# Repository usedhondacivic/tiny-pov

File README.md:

# tiny-pov

Work in progress, check back soon for more.

[Checkout the GUI](http://michael-crum.com/tiny-pov/) for a sneak peak.

Tiny-pov is a low cost, high performance, persistence of vision display built with the STM32G0.
This project is designed to explore cost effective and easily manufacturable mechatronic design.

I currently plan to use a STM32G0 to relay data from a SD Card directly into a string of APA102 LEDs. The arm will be inductively powered using custom coils.

See my first revision of the POV display here: https://github.com/usedhondacivic/ECE-4760-POV-Display

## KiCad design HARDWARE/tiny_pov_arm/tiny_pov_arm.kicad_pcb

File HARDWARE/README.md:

# Hardware

The Tiny-pov circuit boards were designed using [SKiDL](https://devbisme.github.io/skidl/), a python library for generating KiCAD schematics from python code. 
The SKiDL source code for the PCBs is found in `arm_board.py` and `motor_board.py`. The KiCAD symbol and schematic libraries for all components is included, so it should run without any hassle.

```cd HARDWARE && python3 arm_board.py```

For power delivery, I designed a custom 3D printed inductive power coupling inspired by electric toothbrushes. It uses a core of [ferrous 3D printer filament](https://proto-pasta.com/products/magnetic-iron-pla) to increase the efficiency of transformer.
You can find the design files on [OnShape](https://cad.onshape.com/documents/c43b3a736df7726a49e53755/w/ad83221bbc41dda85aa40265/e/0c03297652a8e1a4c52ec09d?renderMode=0&uiState=655283aa916fc55b212fd806).

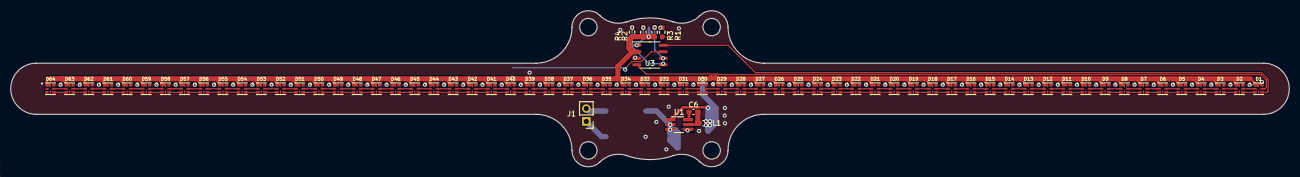
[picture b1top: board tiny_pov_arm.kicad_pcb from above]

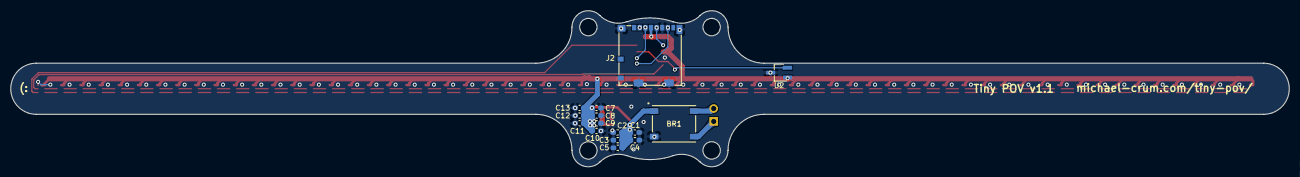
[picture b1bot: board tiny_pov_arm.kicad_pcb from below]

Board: 2 copper layers, 250.0 x 30.5 mm, 88 parts (15 on the bottom side), 140 nets.

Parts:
BR1: DBF310-13; DBF_DIO
C1, C2, C3, C4, C5, C7, C8, C9, C10, C11, C12, C13: 22 uF; C_0603_hand_solder
C6: 100 nF; C_0603_hand_solder
D1, D2, D3, D4, D5, D6, D7, D8, D9, D10, D11, D12, D13, D14, D15, D16, D17, D18, D19, D20, D21, D22, D23, D24, D25, D26, D27, D28, D29, D30, D31, D32, D33, D34, D35, D36, D37, D38, D39, D40, D41, D42, D43, D44, D45, D46, D47, D48, D49, D50, D51, D52, D53, D54, D55, D56, D57, D58, D59, D60, D61, D62, D63, D64: APA102-2020; LED_APA-102-2020-256-8
J1: Conn_01x02_Socket; PinHeader_1x02
J2: SdHolder; microSD
L1: 6.8uH; L_0603_hand_solder
R1: 10k; R_0603_hand_solder
R2, R3, R4: 47k; R_0603_hand_solder
U1: AP63203WU; TSOT-23-6_HandSoldering
U2: AH1806W; SC-59_Handsoldering
U3: STM32G030J6Mx; STM32_SO_8N

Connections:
BST: C6.1, U1.6
GND: BR1.3, C1.2, C2.2, C3.2, C4.2, C5.2, C7.2, C8.2, C9.2, C10.2, C11.2, C12.2, C13.2, D1.6, D2.6, D3.6, D4.6, D5.6, D6.6, D7.6, D8.6, D9.6, D10.6, D11.6, D12.6, D13.6, D14.6, D15.6, D16.6, D17.6, D18.6, D19.6, D20.6, D21.6, D22.6, D23.6, D24.6, D25.6, D26.6, D27.6, D28.6, D29.6, D30.6, D31.6, D32.6, D33.6, D34.6, D35.6, D36.6, D37.6, D38.6, D39.6, D40.6, D41.6, D42.6, D43.6, D44.6, D45.6, D46.6, D47.6, D48.6, D49.6, D50.6, D51.6, D52.6, D53.6, D54.6, D55.6, D56.6, D57.6, D58.6, D59.6, D60.6, D61.6, D62.6, D63.6, D64.6, J2.6, J2.11, R1.1, U1.4, U2.3, U3.3
HALL_DATA: U2.2, U3.7
LED_CLK: D1.5, U3.4
LED_DATA: D1.4, U3.8
SD_CS: J2.2, R1.2
SD_MISO: J2.7, R4.1, U3.5
SD_MOSI: J2.3, R3.1, U3.6
SD_SCK: J2.5, R2.1, U3.1
SW: C6.2, L1.1, U1.5
V_rect_plus: BR1.1, C1.1, C2.1, C3.1, C4.1, C5.1, U1.2, U1.3
Vac_a: BR1.4, J1.1
Vac_b: BR1.2, J1.2
Vdd: C7.1, C8.1, C9.1, C10.1, C11.1, C12.1, C13.1, D1.1, D2.1, D3.1, D4.1, D5.1, D6.1, D7.1, D8.1, D9.1, D10.1, D11.1, D12.1, D13.1, D14.1, D15.1, D16.1, D17.1, D18.1, D19.1, D20.1, D21.1, D22.1, D23.1, D24.1, D25.1, D26.1, D27.1, D28.1, D29.1, D30.1, D31.1, D32.1, D33.1, D34.1, D35.1, D36.1, D37.1, D38.1, D39.1, D40.1, D41.1, D42.1, D43.1, D44.1, D45.1, D46.1, D47.1, D48.1, D49.1, D50.1, D51.1, D52.1, D53.1, D54.1, D55.1, D56.1, D57.1, D58.1, D59.1, D60.1, D61.1, D62.1, D63.1, D64.1, J2.4, L1.2, R2.2, R3.2, R4.2, U1.1, U2.1, U3.2
apa_led_0_1_CK: D1.2, D2.5
apa_led_0_1_SD: D1.3, D2.4
apa_led_1_2_CK: D2.2, D3.5
apa_led_1_2_SD: D2.3, D3.4
apa_led_2_3_CK: D3.2, D4.5
apa_led_2_3_SD: D3.3, D4.4
apa_led_3_4_CK: D4.2, D5.5
apa_led_3_4_SD: D4.3, D5.4
apa_led_4_5_CK: D5.2, D6.5
apa_led_4_5_SD: D5.3, D6.4
apa_led_5_6_CK: D6.2, D7.5
apa_led_5_6_SD: D6.3, D7.4
apa_led_6_7_CK: D7.2, D8.5
apa_led_6_7_SD: D7.3, D8.4
apa_led_7_8_CK: D8.2, D9.5
apa_led_7_8_SD: D8.3, D9.4
apa_led_8_9_CK: D9.2, D10.5
apa_led_8_9_SD: D9.3, D10.4
apa_led_9_10_CK: D10.2, D11.5
apa_led_9_10_SD: D10.3, D11.4
apa_led_10_11_CK: D11.2, D12.5
apa_led_10_11_SD: D11.3, D12.4
apa_led_11_12_CK: D12.2, D13.5
apa_led_11_12_SD: D12.3, D13.4
apa_led_12_13_CK: D13.2, D14.5
apa_led_12_13_SD: D13.3, D14.4
apa_led_13_14_CK: D14.2, D15.5
apa_led_13_14_SD: D14.3, D15.4
apa_led_14_15_CK: D15.2, D16.5
apa_led_14_15_SD: D15.3, D16.4
apa_led_15_16_CK: D16.2, D17.5
apa_led_15_16_SD: D16.3, D17.4
apa_led_16_17_CK: D17.2, D18.5
apa_led_16_17_SD: D17.3, D18.4
apa_led_17_18_CK: D18.2, D19.5
apa_led_17_18_SD: D18.3, D19.4
apa_led_18_19_CK: D19.2, D20.5
apa_led_18_19_SD: D19.3, D20.4
apa_led_19_20_CK: D20.2, D21.5
apa_led_19_20_SD: D20.3, D21.4
apa_led_20_21_CK: D21.2, D22.5
apa_led_20_21_SD: D21.3, D22.4
apa_led_21_22_CK: D22.2, D23.5
apa_led_21_22_SD: D22.3, D23.4
apa_led_22_23_CK: D23.2, D24.5
apa_led_22_23_SD: D23.3, D24.4
apa_led_23_24_CK: D24.2, D25.5
apa_led_23_24_SD: D24.3, D25.4
apa_led_24_25_CK: D25.2, D26.5
apa_led_24_25_SD: D25.3, D26.4
apa_led_25_26_CK: D26.2, D27.5
apa_led_25_26_SD: D26.3, D27.4
apa_led_26_27_CK: D27.2, D28.5
apa_led_26_27_SD: D27.3, D28.4
apa_led_27_28_CK: D28.2, D29.5
apa_led_27_28_SD: D28.3, D29.4
apa_led_28_29_CK: D29.2, D30.5
apa_led_28_29_SD: D29.3, D30.4
apa_led_29_30_CK: D30.2, D31.5
apa_led_29_30_SD: D30.3, D31.4
apa_led_30_31_CK: D31.2, D32.5
apa_led_30_31_SD: D31.3, D32.4
apa_led_31_32_CK: D32.2, D33.5
apa_led_31_32_SD: D32.3, D33.4
apa_led_32_33_CK: D33.2, D34.5
apa_led_32_33_SD: D33.3, D34.4
apa_led_33_34_CK: D34.2, D35.5
apa_led_33_34_SD: D34.3, D35.4
apa_led_34_35_CK: D35.2, D36.5
apa_led_34_35_SD: D35.3, D36.4
apa_led_35_36_CK: D36.2, D37.5
apa_led_35_36_SD: D36.3, D37.4
apa_led_36_37_CK: D37.2, D38.5
apa_led_36_37_SD: D37.3, D38.4
apa_led_37_38_CK: D38.2, D39.5
apa_led_37_38_SD: D38.3, D39.4
apa_led_38_39_CK: D39.2, D40.5
apa_led_38_39_SD: D39.3, D40.4
apa_led_39_40_CK: D40.2, D41.5
apa_led_39_40_SD: D40.3, D41.4
apa_led_40_41_CK: D41.2, D42.5
apa_led_40_41_SD: D41.3, D42.4
apa_led_41_42_CK: D42.2, D43.5
apa_led_41_42_SD: D42.3, D43.4
apa_led_42_43_CK: D43.2, D44.5
apa_led_42_43_SD: D43.3, D44.4
apa_led_43_44_CK: D44.2, D45.5
apa_led_43_44_SD: D44.3, D45.4
apa_led_44_45_CK: D45.2, D46.5
apa_led_44_45_SD: D45.3, D46.4
apa_led_45_46_CK: D46.2, D47.5
apa_led_45_46_SD: D46.3, D47.4
apa_led_46_47_CK: D47.2, D48.5
apa_led_46_47_SD: D47.3, D48.4
apa_led_47_48_CK: D48.2, D49.5
apa_led_47_48_SD: D48.3, D49.4
apa_led_48_49_CK: D49.2, D50.5
apa_led_48_49_SD: D49.3, D50.4
apa_led_49_50_CK: D50.2, D51.5
apa_led_49_50_SD: D50.3, D51.4
apa_led_50_51_CK: D51.2, D52.5
apa_led_50_51_SD: D51.3, D52.4
apa_led_51_52_CK: D52.2, D53.5
apa_led_51_52_SD: D52.3, D53.4
apa_led_52_53_CK: D53.2, D54.5
apa_led_52_53_SD: D53.3, D54.4
apa_led_53_54_CK: D54.2, D55.5
apa_led_53_54_SD: D54.3, D55.4
apa_led_54_55_CK: D55.2, D56.5
apa_led_54_55_SD: D55.3, D56.4
apa_led_55_56_CK: D56.2, D57.5
apa_led_55_56_SD: D56.3, D57.4
apa_led_56_57_CK: D57.2, D58.5
apa_led_56_57_SD: D57.3, D58.4
apa_led_57_58_CK: D58.2, D59.5
apa_led_57_58_SD: D58.3, D59.4
apa_led_58_59_CK: D59.2, D60.5
apa_led_58_59_SD: D59.3, D60.4
apa_led_59_60_CK: D60.2, D61.5
apa_led_59_60_SD: D60.3, D61.4
apa_led_60_61_CK: D61.2, D62.5
apa_led_60_61_SD: D61.3, D62.4
apa_led_61_62_CK: D62.2, D63.5
apa_led_61_62_SD: D62.3, D63.4
apa_led_62_63_CK: D63.2, D64.5
apa_led_62_63_SD: D63.3, D64.4

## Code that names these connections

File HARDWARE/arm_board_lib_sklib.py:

from skidl import Pin, Part, Alias, SchLib, SKIDL, TEMPLATE

SKIDL_lib_version = '0.0.1'

arm_board_lib = SchLib(tool=SKIDL).add_parts(*[
        Part(**{ 'name':'Conn_01x02_Socket', 'dest':TEMPLATE, 'tool':SKIDL, 'datasheet':'~', '_name':'Conn_01x02_Socket', '_aliases':Alias({'Conn_01x02_Socket'}), '_match_pin_regex':False, 'description':'Generic connector, single row, 01x02, script generated', 'keywords':'connector', 'ref_prefix':'J', 'num_units':None, 'fplist':[''], 'do_erc':True, 'aliases':Alias({'Conn_01x02_Socket'}), 'pin':None, 'footprint':'tiny_pov_footprints:PinHeader_1x02', 'pins':[
            Pin(num='1',name='Pin_1',func=Pin.types.PASSIVE,do_erc=True),
            Pin(num='2',name='Pin_2',func=Pin.types.PASSIVE,do_erc=True)] }),
        Part(**{ 'name':'DBF310-13', 'dest':TEMPLATE, 'tool':SKIDL, 'datasheet':'DBF310-13', '_name':'DBF310-13', '_aliases':Alias({'DBF310-13'}), '_match_pin_regex':False, 'description':'', 'keywords':'DBF310-13', 'ref_prefix':'BR', 'num_units':None, 'fplist':['DBF_DIO'], 'do_erc':True, 'aliases':Alias({'DBF310-13'}), 'pin':None, 'footprint':'tiny_pov_footprints:DBF_DIO', 'pins':[
            Pin(num='1',name='V+',func=Pin.types.PWROUT,do_erc=True),
            Pin(num='2',name='Vac_b',func=Pin.types.PWRIN,do_erc=True),
            Pin(num='3',name='V-',func=Pin.types.PWROUT,do_erc=True),
            Pin(num='4',name='Vac_a',func=Pin.types.PWRIN,do_erc=True)] }),
        Part(**{ 'name':'C', 'dest':TEMPLATE, 'tool':SKIDL, 'datasheet':'~', '_name':'C', '_aliases':Alias({'C'}), '_match_pin_regex':False, 'description':'Unpolarized capacitor', 'keywords':'cap capacitor', 'ref_prefix':'C', 'num_units':None, 'fplist':[''], 'do_erc':True, 'aliases':Alias({'C'}), 'pin':None, 'footprint':'tiny_pov_footprints:C_0603_hand_solder', 'pins':[
            Pin(num='1',name='~',func=Pin.types.PASSIVE,do_erc=True),
            Pin(num='2',name='~',func=Pin.types.PASSIVE,do_erc=True)] }),
        Part(**{ 'name':'AP63203WU', 'dest':TEMPLATE, 'tool':SKIDL, 'datasheet':'https://www.diodes.com/assets/Datasheets/AP63200-AP63201-AP63203-AP63205.pdf', '_name':'AP63203WU', '_aliases':Alias({'AP63203WU'}), '_match_pin_regex':False, 'description':'2A, 1.1MHz Buck DC/DC Converter, fixed 3.3V output voltage, TSOT-23-6', 'keywords':'2A Buck DC/DC', 'ref_prefix':'U', 'num_units':None, 'fplist':['Package_TO_SOT_SMD:TSOT-23-6'], 'do_erc':True, 'aliases':Alias({'AP63203WU'}), 'pin':None, 'footprint':'tiny_pov_footprints:TSOT-23-6_HandSoldering', 'pins':[
            Pin(num='1',name='FB',func=Pin.types.INPUT,do_erc=True),
            Pin(num='2',name='EN',func=Pin.types.INPUT,do_erc=True),
            Pin(num='3',name='VIN',func=Pin.types.PWRIN,do_erc=True),
            Pin(num='4',name='GND',func=Pin.types.PWRIN,do_erc=True),
            Pin(num='5',name='SW',func=Pin.types.OUTPUT,do_erc=True),
            Pin(num='6',name='BST',func=Pin.types.PASSIVE,do_erc=True)] }),
        Part(**{ 'name':'L', 'dest':TEMPLATE, 'tool':SKIDL, 'datasheet':'~', '_name':'L', '_aliases':Alias({'L'}), '_match_pin_regex':False, 'description':'Inductor', 'keywords':'inductor choke coil reactor magnetic', 'ref_prefix':'L', 'num_units':None, 'fplist':[''], 'do_erc':True, 'aliases':Alias({'L'}), 'pin':None, 'footprint':'tiny_pov_footprints:L_0603_hand_solder', 'pins':[
            Pin(num='1',name='1',func=Pin.types.PASSIVE,do_erc=True),
            Pin(num='2',name='2',func=Pin.types.PASSIVE,do_erc=True)] }),
        Part(**{ 'name':'APA102-2020', 'dest':TEMPLATE, 'tool':SKIDL, 'datasheet':'http://www.led-color.com/upload/201604/APA102-2020%20SMD%20LED.pdf', '_name':'APA102-2020', '_aliases':Alias({'APA102-2020'}), '_match_pin_regex':False, 'description':'RGB LED with integrated controller', 'keywords':'RGB LED addressable 8bit pwm 5bit greyscale', 'ref_prefix':'D', 'num_units':None, 'fplist':['LED_SMD:LED-APA102-2020'], 'do_erc':True, 'aliases':Alias({'APA102-2020'}), 'pin':None, 'footprint':'tiny_pov_footprints:LED_APA-102-2020-256-8', 'pins':[
            Pin(num='1',name='VDD',func=Pin.types.PWRIN,do_erc=True),
            Pin(num='2',name='CKO',func=Pin.types.OUTPUT,do_erc=True),
            Pin(num='3',name='SDO',func=Pin.types.OUTPUT,do_erc=True),
            Pin(num='4',name='SDI',func=Pin.types.INPUT,do_erc=True),
            Pin(num='5',name='CKI',func=Pin.types.INPUT,do_erc=True),
            Pin(num='6',name='GND',func=Pin.types.PWRIN,do_erc=True)] }),
        Part(**{ 'name':'SdHolder', 'dest':TEMPLATE, 'tool':SKIDL, 'datasheet':'1040310811', '_name':'SdHolder', '_aliases':Alias({'SdHolder'}), '_match_pin_regex':False, 'description':'', 'keywords':'1040310811', 'ref_prefix':'J', 'num_units':None, 'fplist':['104031-0811_MOL'], 'do_erc':True, 'aliases':Alias({'SdHolder'}), 'pin':None, 'footprint':'tiny_pov_footprints:microSD', 'pins':[
            Pin(num='4',name='VDD',func=Pin.types.PWRIN,do_erc=True),
            Pin(num='1',name='DAT2',func=Pin.types.NOCONNECT,do_erc=True),
            Pin(num='10',name='SW_DETECT',func=Pin.types.NOCONNECT,do_erc=True),
            Pin(num='11',name='SHIELD',func=Pin.types.PWRIN,do_erc=True),
            Pin(num='2',name='CS',func=Pin.types.INPUT,do_erc=True),
            Pin(num='3',name='MOSI',func=Pin.types.INPUT,do_erc=True),
            Pin(num='5',name='SCK',func=Pin.types.INPUT,do_erc=True),
            Pin(num='6',name='GND',func=Pin.types.PWRIN,do_erc=True),
            Pin(num='7',name='MISO',func=Pin.types.OUTPUT,do_erc=True),
            Pin(num='8',name='DAT1',func=Pin.types.NOCONNECT,do_erc=True),
            Pin(num='9',name='SW_DETECT',func=Pin.types.NOCONNECT,do_erc=True)] }),
        Part(**{ 'name':'R', 'dest':TEMPLATE, 'tool':SKIDL, 'datasheet':'~', '_name':'R', '_aliases':Alias({'R'}), '_match_pin_regex':False, 'description':'Resistor', 'keywords':'R res resistor', 'ref_prefix':'R', 'num_units':None, 'fplist':[''], 'do_erc':True, 'aliases':Alias({'R'}), 'pin':None, 'footprint':'tiny_pov_footprints:R_0603_hand_solder', 'pins':[
            Pin(num='1',name='~',func=Pin.types.PASSIVE,do_erc=True),
            Pin(num='2',name='~',func=Pin.types.PASSIVE,do_erc=True)] }),
        Part(**{ 'name':'AH1806W', 'dest':TEMPLATE, 'tool':SKIDL, 'datasheet':'https://www.diodes.com/assets/Datasheets/AH1806.pdf', '_name':'AH1806W', '_aliases':Alias({'AH1806W'}), '_match_pin_regex':False, 'description':'High Sensitivity Micropower Omnipolar Hall-Effect Switch, SC-59', 'keywords':'hall switch', 'ref_prefix':'U', 'num_units':None, 'fplist':['Package_TO_SOT_SMD:SC-59'], 'do_erc':True, 'aliases':Alias({'AH1806W'}), 'pin':None, 'footprint':'tiny_pov_footprints:SC-59_Handsoldering', 'pins':[
            Pin(num='1',name='VDD',func=Pin.types.PWRIN,do_erc=True),
            Pin(num='2',name='OUTPUT',func=Pin.types.OUTPUT,do_erc=True),
            Pin(num='3',name='GND',func=Pin.types.PWRIN,do_erc=True)] }),
        Part(**{ 'name':'STM32G030J6Mx', 'dest':TEMPLATE, 'tool':SKIDL, 'datasheet':'https://www.st.com/resource/en/datasheet/stm32g030j6.pdf', '_name':'STM32G030J6Mx', '_aliases':Alias({'STM32G030J6Mx'}), '_match_pin_regex':False, 'description':'STMicroelectronics Arm Cortex-M0+ MCU, 32KB flash, 8KB RAM, 64 MHz, 2.0-3.6V, 6 GPIO, SO8N', 'keywords':'Arm Cortex-M0+ STM32G0 STM32G0x0 Value line', 'ref_prefix':'U', 'num_units':None, 'fplist':['Package_SO:SOIC-8_3.9x4.9mm_P1.27mm'], 'do_erc':True, 'aliases':Alias({'STM32G030J6Mx'}), 'pin':None, 'footprint':'tiny_pov_footprints:STM32_SO_8N', 'pins':[
            Pin(num='1',name='PC14/PB7/PB8/PB9',func=Pin.types.BIDIR,do_erc=True),
            Pin(num='2',name='VDD',func=Pin.types.PWRIN,do_erc=True),
            Pin(num='3',name='VSS',func=Pin.types.PWRIN,do_erc=True),
            Pin(num='4',name='NRST/PA0/PA1/PA2',func=Pin.types.BIDIR,do_erc=True),
            Pin(num='5',name='PB0/PB1/PA8/PA11/PA9',func=Pin.types.BIDIR,do_erc=True),
            Pin(num='6',name='PA12/PA10',func=Pin.types.BIDIR,do_erc=True),
            Pin(num='7',name='PA13',func=Pin.types.BIDIR,do_erc=True),
            Pin(num='8',name='PA14/PA15/PB5/PB6',func=Pin.types.BIDIR,do_erc=True)] })])

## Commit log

2023-11-08 init
2023-11-08 Added README
2023-11-09 Broke SPI driver out into library
2023-11-09 Fixed some formatting
2023-11-09 Restructured project
2023-11-09 Started work on GUI
2023-11-09 Spelling and formatting fixes for GUI
2023-11-09 Updated readme's
2023-11-10 The clang-formatening
2023-11-10 Re: The clang-formatening
2023-11-10 Updates to GUI layout
2023-11-10 Renamed GUI to docs to make github pages happy
2023-11-10 Added fade out to top and bottom of menu
2023-11-12 Implemented preview rendering
2023-11-12 Implemented file output
2023-11-12 Fixed spelling issues in GUI
2023-11-12 Added viewport for mobile optimization
2023-11-13 Fixed screen width issue on mobile
2023-11-13 Started SKiDL board implementation
2023-11-14 Added footprints, symbols, more work on SKiDL board
2023-11-14 Completed V1 of SKiDL schematic
2023-11-14 Completed V1 arm board layout
2023-11-18 Rip attiny
2023-11-21 Start STM32 development
2023-11-21 House keeping
2023-12-23 Iterated board layout
2023-12-23 v1 board ordered
2023-12-23 Fix typos in readme
2023-12-23 Cleaned up node module reminants
2023-12-24 Fix error with mm scaling
2023-12-24 STM32G0 blinking
2023-12-28 Increased clock speed to 64 MHz
2023-12-28 cleaning up
2023-12-28 implemented systick
2023-12-28 clean up
2023-12-29 apa102 driver working
2023-12-29 Added pretty apa102 example
2024-01-02 Changed apa102 to correct footprint, changed STM32 pinout to allow for SPI
2024-01-05 Option bit configuration working
2024-01-05 apa102 over spi working
2024-01-05 Cleaned up apa102 driver
2024-01-07 SD card intialization working
2024-01-07 SD card init actually working
2024-01-08 Moved SPI to seperate driver
2024-01-08 SD block read implemented, verified on SD card BPB
2024-01-09 Updated pinout to support SD and APA102 at the same time
2024-01-09 Update help link on website
2024-01-10 Fixed bug in docs
2024-01-10 Revamped SD block reads
2024-01-11 FAT driver can now read root directory
2024-01-11 Added README to FIRMWARE
2024-01-11 Work on finding files in FAT driver
2024-01-12 Arm board v1.1
2024-01-16 FAT file locating working
2024-01-16 Gerbers for v1.1 order
2024-01-17 Single block image data read working
2024-01-17 More robust naming conventions + brightness byte
2024-01-31 Change RGB to BGR for APA102 compatibility
